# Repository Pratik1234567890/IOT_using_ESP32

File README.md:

# IOT_using_ESP32

This is four layer circuit board

# Schmematic

# 3D viewer

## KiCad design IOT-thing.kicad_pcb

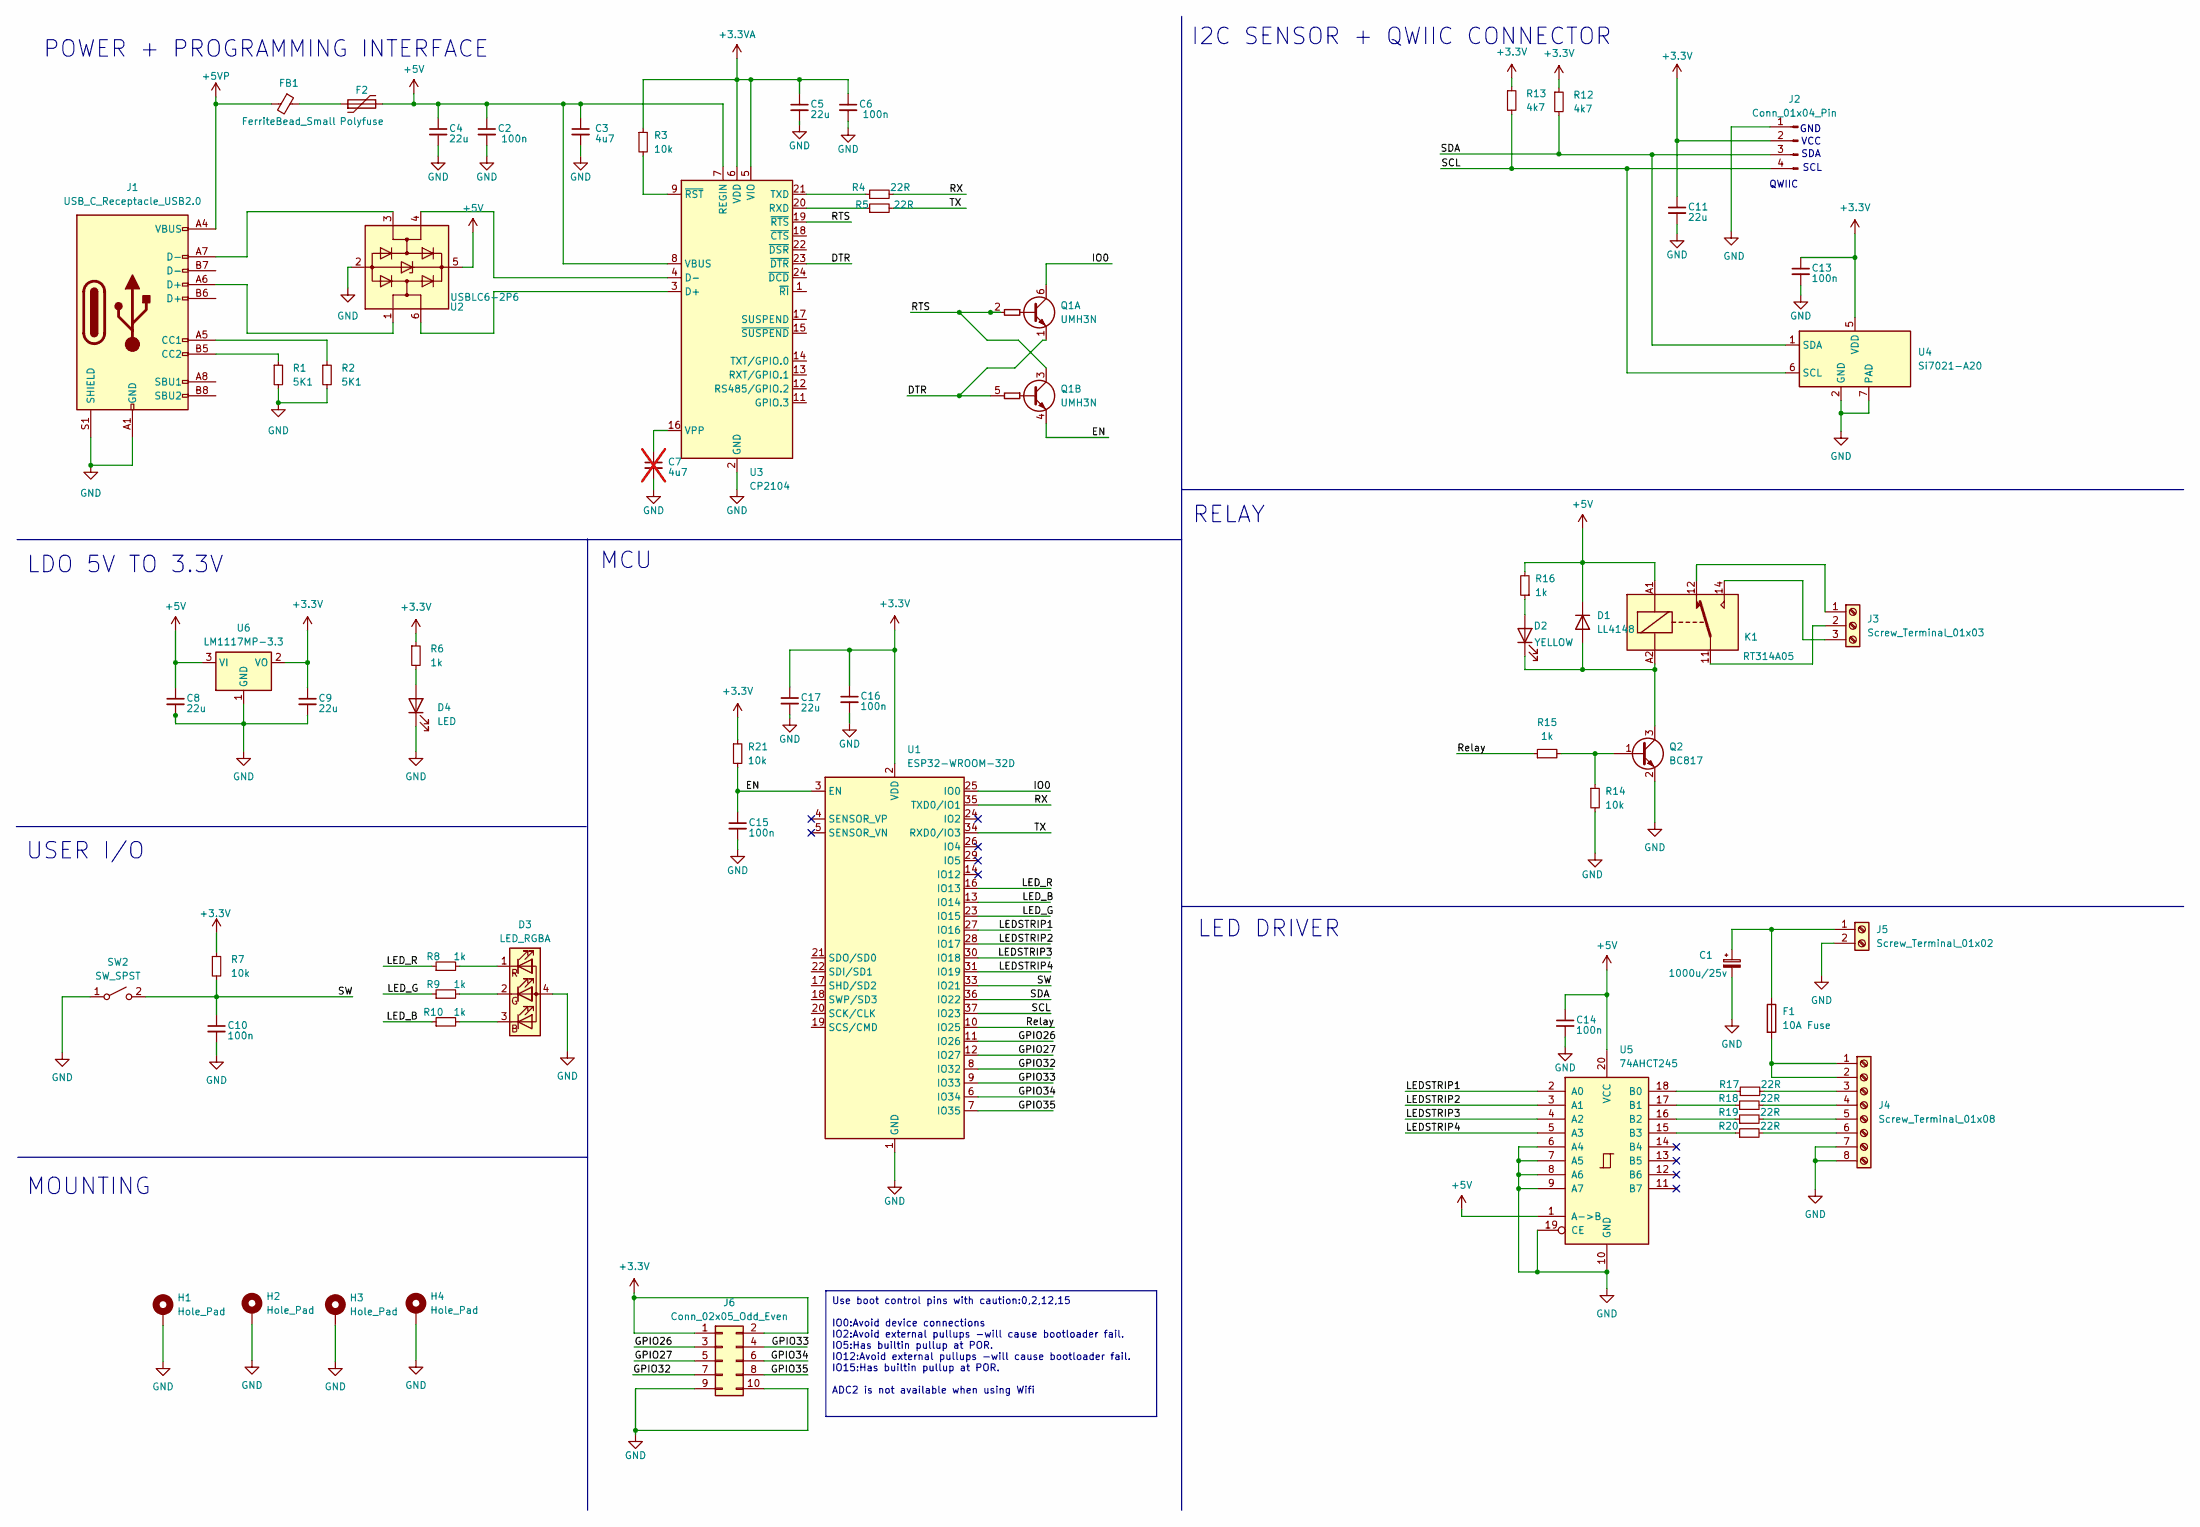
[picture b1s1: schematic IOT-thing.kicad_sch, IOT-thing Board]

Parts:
C1: 1000u/25v; CP_Radial_D10.0mm_P5.00mm
C2, C6, C10, C13, C14, C15, C16: 100n; C_0402_1005Metric_Pad0.74x0.62mm_HandSolder
C3: 4u7; C_0805_2012Metric_Pad1.18x1.45mm_HandSolder
C4, C5, C8, C9, C11, C17: 22u; C_0805_2012Metric_Pad1.18x1.45mm_HandSolder
C7: 4u7; C_0805_2012Metric_Pad1.18x1.45mm_HandSolder; not fitted
D1: LL4148; D_MiniMELF
D2: YELLOW; LED_0603_1608Metric_Pad1.05x0.95mm_HandSolder
D3: LED_RGBA; LED_RGB_Wuerth-PLCC4_3.2x2.8mm_150141M173100
D4: LED; LED_0603_1608Metric_Pad1.05x0.95mm_HandSolder
F1: 10A Fuse; Fuseholder_Clip-5x20mm_Bel_FC-203-22_Lateral_P17.80x5.00mm_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
F2: Polyfuse; Fuse_1206_3216Metric_Pad1.42x1.75mm_HandSolder
FB1: FerriteBead_Small; L_0603_1608Metric_Pad1.05x0.95mm_HandSolder
H1, H2, H3, H4: Hole_Pad; MountingHole_3.2mm_M3_Pad_Via
J1: USB_C_Receptacle_USB2.0; USB_C_Receptacle_HRO_TYPE-C-31-M-12
J2: Conn_01x04_Pin; JST_SH_SM04B-SRSS-TB_1x04-1MP_P1.00mm_Horizontal
J3: Screw_Terminal_01x03; TerminalBlock_Phoenix_MKDS-3-3-5.08_1x03_P5.08mm_Horizontal
J4: Screw_Terminal_01x08; TerminalBlock_Phoenix_MKDS-1,5-8_1x08_P5.00mm_Horizontal
J5: Screw_Terminal_01x02; TerminalBlock_Phoenix_MKDS-1,5-2-5.08_1x02_P5.08mm_Horizont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
J6: Conn_02x05_Odd_Even; PinHeader_2x05_P2.54mm_Vertical
K1: RT314A05; Relay_SPDT_Schrack-RT1-16A-FormC_RM5mm
Q1: UMH3N; SOT-363_SC-70-6
Q2: BC817; SOT-23
R1, R2: 5K1; R_0402_1005Metric_Pad0.72x0.64mm_HandSolder
R3, R7, R14, R21: 10k; R_0402_1005Metric_Pad0.72x0.64mm_HandSolder
R4, R5, R17, R18, R19, R20: 22R; R_0402_1005Metric_Pad0.72x0.64mm_HandSolder
R6, R8, R9, R10, R15, R16: 1k; R_0402_1005Metric_Pad0.72x0.64mm_HandSolder
R12, R13: 4k7; R_0402_1005Metric_Pad0.72x0.64mm_HandSolder
SW2: SW_SPST; SW_Push_1P1T_NO_6x6mm_H9.5mm
U1: ESP32-WROOM-32D
U2: USBLC6-2P6; SOT-666
U3: CP2104; QFN-24-1EP_4x4mm_P0.5mm_EP2.6x2.6mm
U4: Si7021-A20; DFN-6-1EP_3x3mm_P1mm_EP1.5x2.4mm
U5: 74AHCT245; DIP-20_W7.62mm
U6: LM1117MP-3.3; SOT-223-3_TabPin2

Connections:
+3.3V: C9.1, C11.1, C13.1, C16.1, C17.1, J2.2, J6.1, J6.2, R6.1, R7.1, R12.1, R13.1, R21.1, U1.2 (VDD), U4.5 (VDD), U6.2 (VO)
+3.3VA: C5.1, C6.1, R3.1, U3.5 (VIO), U3.6 (VDD)
+5V: C2.1, C3.1, C4.1, C8.1, C14.1, D1.1 (K), F2.2, K1.A1, R16.2, U2.5 (VBUS), U3.7 (REGIN), U3.8 (VBUS), U5.1 (A->B), U5.20 (VCC), U6.3 (VI)
+5VP: FB1.2, J1.A4 (VBUS), J1.A9 (VBUS), J1.B4 (VBUS), J1.B9 (VBUS)
/DTR: Q1.1 (E1), Q1.5 (B2), U3.23 (~DTR)
/EN: C15.1, Q1.4 (E2), R21.2, U1.3 (EN)
/GPIO26: J6.3, U1.11 (IO26)
/GPIO27: J6.5, U1.12 (IO27)
/GPIO32: J6.7, U1.8 (IO32)
/GPIO33: J6.4, U1.9 (IO33)
/GPIO34: J6.6, U1.6 (IO34)
/GPIO35: J6.8, U1.7 (IO35)
/IO0: Q1.6 (C1), U1.25 (IO0)
/LEDSTRIP1: U1.27 (IO16), U5.2 (A0)
/LEDSTRIP2: U1.28 (IO17), U5.3 (A1)
/LEDSTRIP3: U1.30 (IO18), U5.4 (A2)
/LEDSTRIP4: U1.31 (IO19), U5.5 (A3)
/LED_B: R10.1, U1.13 (IO14)
/LED_G: R9.1, U1.23 (IO15)
/LED_R: R8.1, U1.16 (IO13)
/RTS: Q1.2 (B1), Q1.3 (C2), U3.19 (~RTS)
/RX: R4.2, U1.35 (TXD0/IO1)
/Relay: R15.1, U1.10 (IO25)
/SCL: J2.4, R13.2, U1.37 (IO23), U4.6 (SCL)
/SDA: J2.3, R12.2, U1.36 (IO22), U4.1 (SDA)
/SW: C10.1, R7.2, SW2.2 (B), U1.33 (IO21)
/TX: R5.2, U1.34 (RXD0/IO3)
GND: C1.2, C2.2, C3.2, C4.2, C5.2, C6.2, C7.2, C8.2, C9.2, C10.2, C11.2, C13.2, C14.2, C15.2, C16.2, C17.2, D3.4 (A), D4.1 (K), H1.1, H2.1, H3.1, H4.1, J1.A1 (GND), J1.A12 (GND), J1.B1 (GND), J1.B12 (GND), J1.S1 (SHIELD), J2.1, J4.7, J4.8, J5.2, J6.9, J6.10, Q2.2 (E), R1.2, R2.2, R14.2, SW2.1 (A), U1.1 (GND), U1.15 (GND), U1.38 (GND), U1.39 (GND), U2.2 (GND), U3.2 (GND), U3.25 (GND), U4.2 (GND), U4.7 (PAD), U5.6 (A4), U5.7 (A5), U5.8 (A6), U5.9 (A7), U5.10 (GND), U5.19 (CE), U6.1 (GND)
unnamed: D1.2 (A), D2.1 (K), K1.A2, Q2.3 (C)
unnamed: D2.2 (A), R16.1
unnamed: D3.3 (BK), R10.2
unnamed: D3.2 (GK), R9.2
unnamed: D3.1 (RK), R8.2
unnamed: D4.2 (A), R6.2
unnamed: F2.1, FB1.1
unnamed: J1.A5 (CC1), R2.1
unnamed: J1.B5 (CC2), R1.1
unnamed: J1.A6 (D+), U2.1 (I/O1)
unnamed: J1.A7 (D-), U2.3 (I/O2)
unnamed: J3.1, K1.12
unnamed: J3.2, K1.11
unnamed: J3.3, K1.14
unnamed: F1.2, J4.1, J4.2
unnamed: J4.3, R17.2
unnamed: J4.4, R18.2
unnamed: J4.5, R19.2
unnamed: J4.6, R20.2
unnamed: C1.1, F1.1, J5.1
unnamed: Q2.1 (B), R14.1, R15.2
unnamed: U2.6 (I/O1), U3.3 (D+)
unnamed: U2.4 (I/O2), U3.4 (D-)
unnamed: R5.1, U3.20 (RXD)
unnamed: R4.1, U3.21 (TXD)
unnamed: C7.1, U3.16 (VPP)
unnamed: R3.2, U3.9 (~RST)
unnamed: R17.1, U5.18 (B0)
unnamed: R18.1, U5.17 (B1)
unnamed: R19.1, U5.16 (B2)
unnamed: R20.1, U5.15 (B3)

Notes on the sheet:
Use boot control pins with caution:0,2,12,15 IO0:Avoid device connections IO2:Avoid external pullups -will cause bootloader fail. IO5:Has builtin pullup at POR. IO12:Avoid external pullups -will cause bootloader fail. IO15:Has builtin pullup at POR. ADC2 is not available when using Wifi
RELAY
I2C SENSOR + QWIIC CONNECTOR
GND
USER I/O
LDO 5V TO 3.3V
POWER + PROGRAMMING INTERFACE
QWIIC
VCC
MCU
SDA
SCL
LED DRIVER
MOUNTING

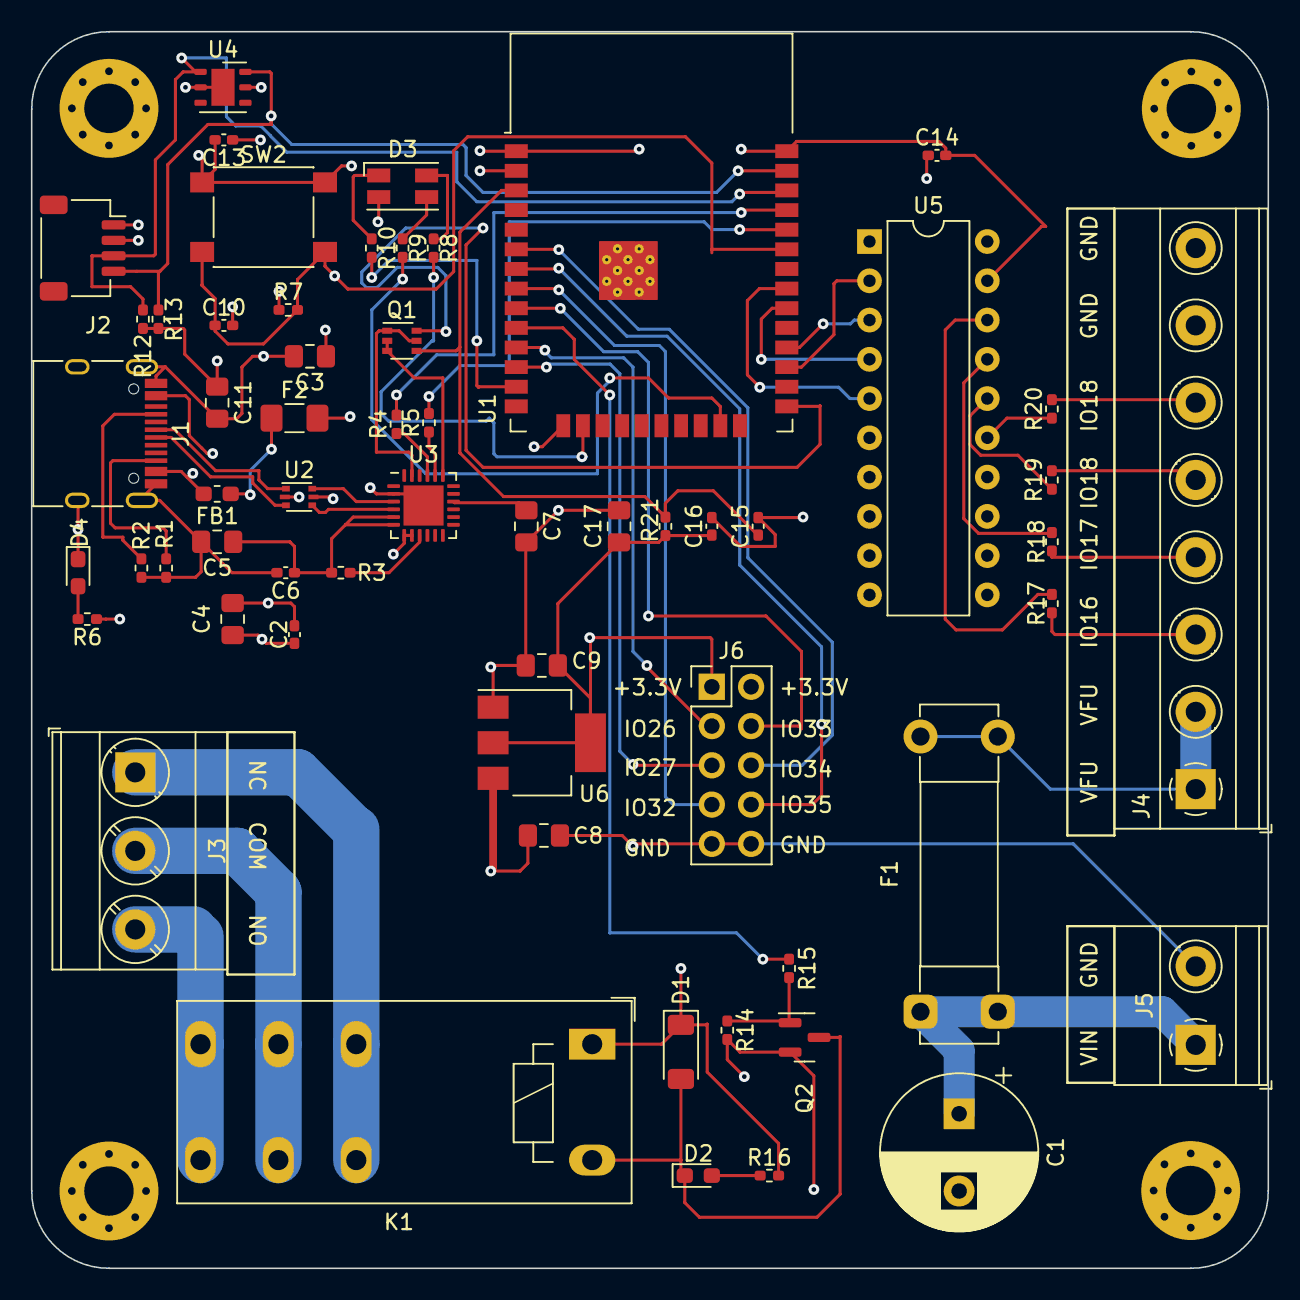
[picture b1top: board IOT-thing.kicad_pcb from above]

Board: 4 copper layers, 80.0 x 80.0 mm, 63 parts (0 on the bottom side), 59 nets.
